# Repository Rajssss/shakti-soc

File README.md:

Central repository for Shakti SoC's
===================================

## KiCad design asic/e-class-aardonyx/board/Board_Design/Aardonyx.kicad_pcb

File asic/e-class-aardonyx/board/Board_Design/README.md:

This design is draft verison it not complete verision. 

This folder contains all board design related files.

## Directory Structure

├── Aardonyx.pro        # Kicad project                     
├── board               # Kicad pcb files for Aardonyx      
├── gerber              # Gerber files for Aardonyx         
├── library             # library(symbols) used for Aardonyx  
├── modules             # moudles(footprint lib, 3d model) used for Aardonyx    
├── schematic           # schematics for Aardonyx

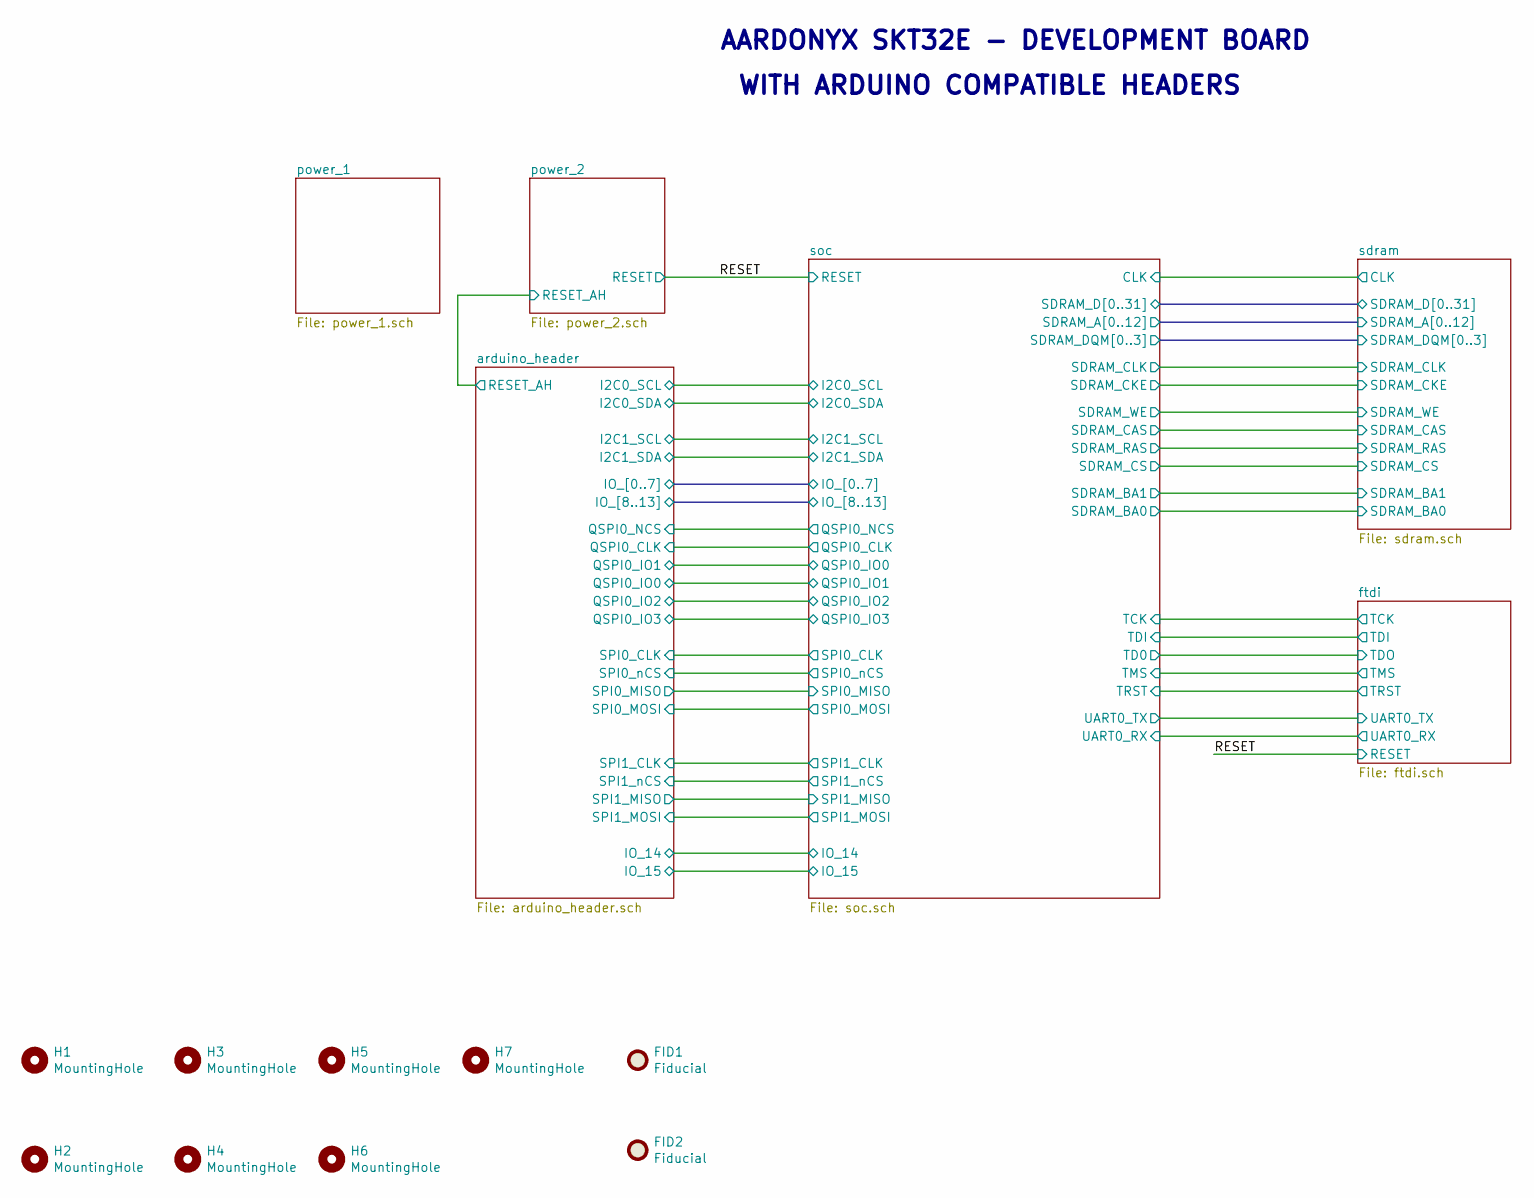
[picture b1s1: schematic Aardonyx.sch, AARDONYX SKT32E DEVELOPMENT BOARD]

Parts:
FID1, FID2: Fiducial; Fiducial_1.5mm_Mask3mm
H1, H2, H3, H4, H5, H6, H7: MountingHole; MountingHole_3.2mm_M3

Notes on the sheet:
AARDONYX SKT32E - DEVELOPMENT BOARD
WITH ARDUINO COMPATIBLE HEADERS

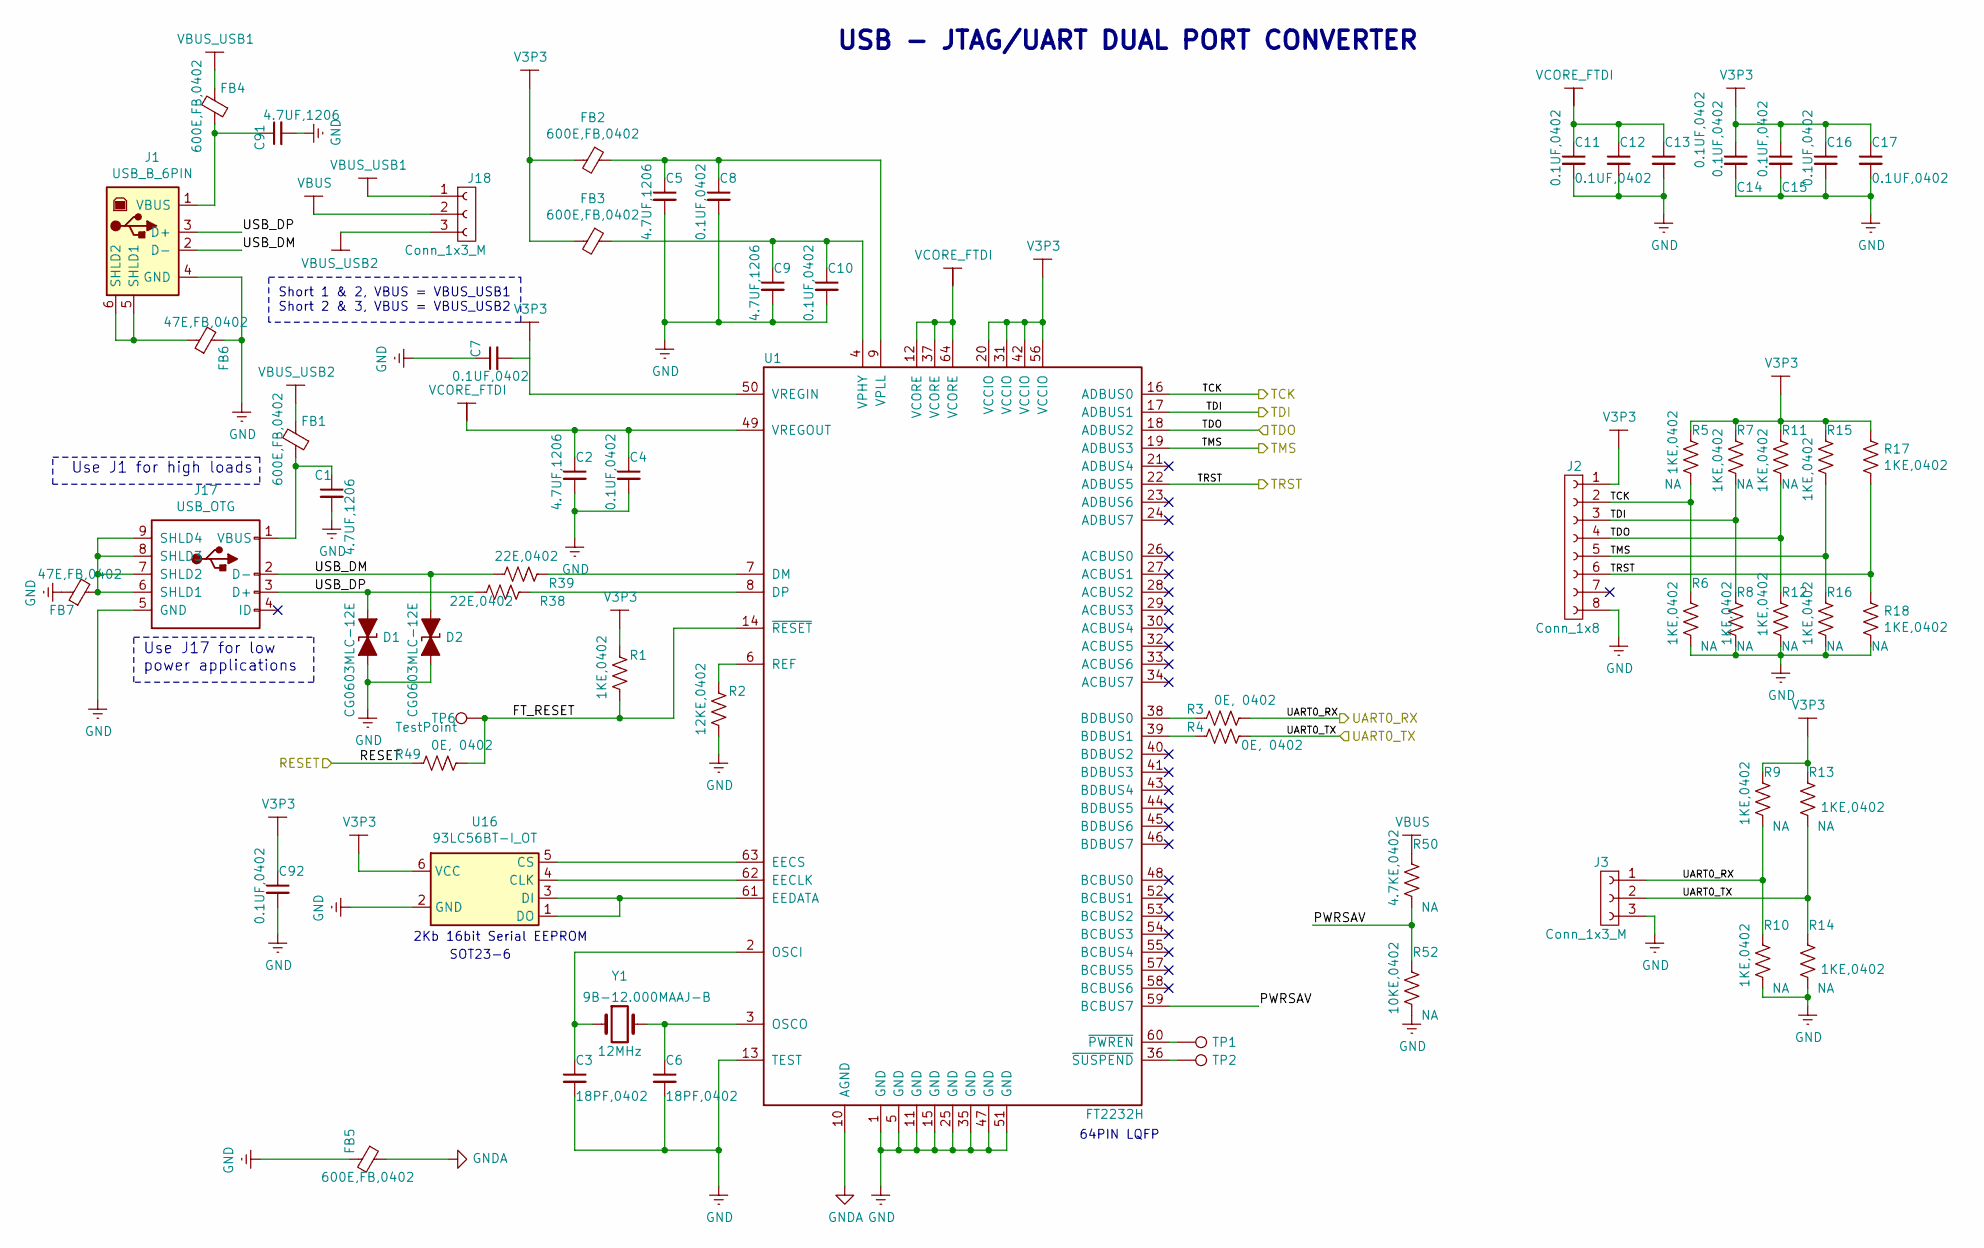
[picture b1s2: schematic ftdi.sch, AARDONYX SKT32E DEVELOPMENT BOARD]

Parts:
C1, C2, C5, C9, C91: 4.7UF,1206; C_1206_3216Metric; Manufactured Part Number T491A475K016AT; Digikey PartNumber 399-18027-1-ND
C3, C6: 18PF,0402; C_0402_1005Metric; Manufactured Part Number CC0201JRNPO9BN180; Digikey PartNumber 311-1386-1-ND
C4, C7, C8, C10, C11, C12, C13, C14, C15, C16, C17, C92: 0.1UF,0402; C_0402_1005Metric; Manufactured Part Number 04023C104JAT2A; Digikey PartNumber 478-10050-1-ND
D1, D2: CG0603MLC-12E; D_0603_1608Metric; Manufactured Part Number CG0603MLC-12E; Digikey PartNumber CG0603MLC-12ECT-ND
FB1, FB2, FB3, FB4, FB5: 600E,FB,0402; L_0402_1005Metric; Manufactured Part Number 7427927291; Digikey PartNumber 732-2388-1-ND
FB6, FB7: 47E,FB,0402; L_0402_1005Metric; Manufactured Part Number 742792608; Digikey PartNumber 732-1596-1-ND
J1: USB_B_6PIN; USB_B_OST_USB-B1HSxx_Horizontal; Manufactured Part Number 61729-0010BLF; Digikey PartNumber 609-1039-ND
J2: Conn_1x8; PinHeader_1x08_P2.54mm_Vertical; Manufactured Part Number 68000-408HLF; Digikey PartNumber 609-3264-ND
J3, J18: Conn_1x3_M; PinHeader_1x03_P2.54mm_Vertical; Manufactured Part Number 68000-203HLF; Digikey PartNumber 609-3464-ND
J17: USB_OTG; USB_Micro-B_Amphenol_10103594-0001LF_Horizontal; Manufactured Part Number 10118194-0001LF; Digikey PartNumber 609-4618-1-ND
R1: 1KE,0402; R_0402_1005Metric; Manufactured Part Number ERJ-2GEJ102X; Digikey PartNumber P1.0KJCT-ND
R2: 12KE,0402; R_0402_1005Metric; Manufactured Part Number ERA-2AEB123X; Digikey PartNumber P12KDCCT-ND
R3, R4, R49: 0E, 0402; R_0402_1005Metric; Manufactured Part Number CRCW04020000Z0ED; Digikey PartNumber 541-0.0JCT-ND
R5, R6, R7, R8, R9, R10, R11, R12, R13, R14, R15, R16, R17, R18: 1KE,0402; R_0402_1005Metric; Manufactured Part Number ERA-2AEB123X; Digikey PartNumber P1.0KJCT-ND
R38, R39: 22E,0402; R_0402_1005Metric; Manufactured Part Number RC0402FR-0722RL; Digikey PartNumber 311-22.0LRCT-ND
R50: 4.7KE,0402; R_0402_1005Metric; Manufactured Part Number RC0402JR-074K7L; Digikey PartNumber 311-4.7KJRCT-ND
R52: 10KE,0402; R_0402_1005Metric; Manufactured Part Number SG73S1ETTP103J; Digikey PartNumber 2019-SG73S1ETTP103JCT-ND
TP1, TP2, TP6: TestPoint; TestPoint_Pad_D1.0mm
U1: FT2232H; LQFP-64_10x10mm_P0.5mm; Manufactured Part Number FT2232HL-REEL; Digikey PartNumber 768-1024-1-ND
U16: 93LC56BT-I_OT; SOT-23-6; Manufactured Part Number 93LC56BT-I/OT; Digikey PartNumber 93LC56BT-I/OTCT-ND
Y1: 12MHz; Crystal_SMD_ROHS_CSM_7XDN_HandSoldering; Manufactured Part Number ECS-120-20-5PXDN-TR; Digikey PartNumber XC1298CT-ND

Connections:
/RESET: R49.1; also elsewhere on the board
/ftdi/FT_RESET: R1.2, R49.2, TP6.1, U1.14 (~RESET)
/ftdi/PWRSAV: R50.2, R52.1, U1.59 (BCBUS7)
/ftdi/TCK: J2.2, R5.2, R6.1, U1.16 (ADBUS0); also elsewhere on the board
/ftdi/TDI: J2.3, R7.2, R8.1, U1.17 (ADBUS1); also elsewhere on the board
/ftdi/TMS: J2.5, R15.2, R16.1, U1.19 (ADBUS3); also elsewhere on the board
/ftdi/TRST: J2.6, R17.2, R18.1, U1.22 (ADBUS5); also elsewhere on the board
/ftdi/UART0_RX: J3.1, R3.2, R9.2, R10.1; also elsewhere on the board
/ftdi/UART0_TX: J3.2, R4.2, R13.2, R14.1; also elsewhere on the board
/ftdi/USB_DM: D2.1 (A1), J1.2 (D-), J17.2 (D-), R39.2
/ftdi/USB_DP: D1.1 (A1), J1.3 (D+), J17.3 (D+), R38.2
/soc/TD0: J2.4, R11.2, R12.1, U1.18 (ADBUS2); also elsewhere on the board
GND: C1.2, C2.2, C3.2, C4.2, C5.2, C6.2, C7.1, C8.2, C9.2, C10.2, C11.2, C12.2, C13.2, C14.2, C15.2, C16.2, C17.2, C91.2, C92.2, D1.2 (A2), D2.2 (A2), FB5.2, FB6.2, FB7.1, J1.4 (GND), J2.8, J3.3, J17.5 (GND), R2.2, R6.2, R8.2, R10.2, R12.2, R14.2, R16.2, R18.2, R52.2, U1.1 (GND), U1.5 (GND), U1.11 (GND), U1.13 (TEST), U1.15 (GND), U1.25 (GND), U1.35 (GND), U1.47 (GND), U1.51 (GND), U16.2 (GND); also elsewhere on the board
GNDA: FB5.1, U1.10 (AGND)
unnamed: C1.1, FB1.1, J17.1 (VBUS)
unnamed: C3.1, U1.2 (OSCI), Y1.1
unnamed: C5.1, C8.1, FB2.1, U1.9 (VPLL)
unnamed: C6.1, U1.3 (OSCO), Y1.2
unnamed: C9.1, C10.1, FB3.1, U1.4 (VPHY)
unnamed: C91.1, FB4.1, J1.1 (VBUS)
unnamed: FB6.1, J1.5 (SHLD1), J1.6 (SHLD2)
unnamed: FB7.2, J17.6 (SHLD1), J17.7 (SHLD2), J17.8 (SHLD3), J17.9 (SHLD4)
unnamed: R2.1, U1.6 (REF)
unnamed: R3.1, U1.38 (BDBUS0)
unnamed: R4.1, U1.39 (BDBUS1)
unnamed: R38.1, U1.8 (DP)
unnamed: R39.1, U1.7 (DM)
unnamed: TP1.1, U1.60 (~PWREN)
unnamed: TP2.1, U1.36 (~SUSPEND)
unnamed: U1.61 (EEDATA), U16.1 (DO), U16.3 (DI)
unnamed: U1.62 (EECLK), U16.4 (CLK)
unnamed: U1.63 (EECS), U16.5 (CS)
V3P3: C7.2, C14.1, C15.1, C16.1, C17.1, C92.1, FB2.2, FB3.2, J2.1, R1.1, R5.1, R7.1, R9.1, R11.1, R13.1, R15.1, R17.1, U1.20 (VCCIO), U1.31 (VCCIO), U1.42 (VCCIO), U1.50 (VREGIN), U1.56 (VCCIO), U16.6 (VCC); also elsewhere on the board
VBUS: J18.2, R50.1; also elsewhere on the board
VBUS_USB1: FB4.2, J18.1
VBUS_USB2: FB1.2, J18.3
VCORE_FTDI: C2.1, C4.1, C11.1, C12.1, C13.1, U1.12 (VCORE), U1.37 (VCORE), U1.49 (VREGOUT), U1.64 (VCORE)

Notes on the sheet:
USB - JTAG/UART DUAL PORT CONVERTER
64PIN LQFP
2Kb 16bit Serial EEPROM
SOT23-6
Short 1 & 2, VBUS = VBUS_USB1 Short 2 & 3, VBUS = VBUS_USB2
Use J1 for high loads
Use J17 for low power applications

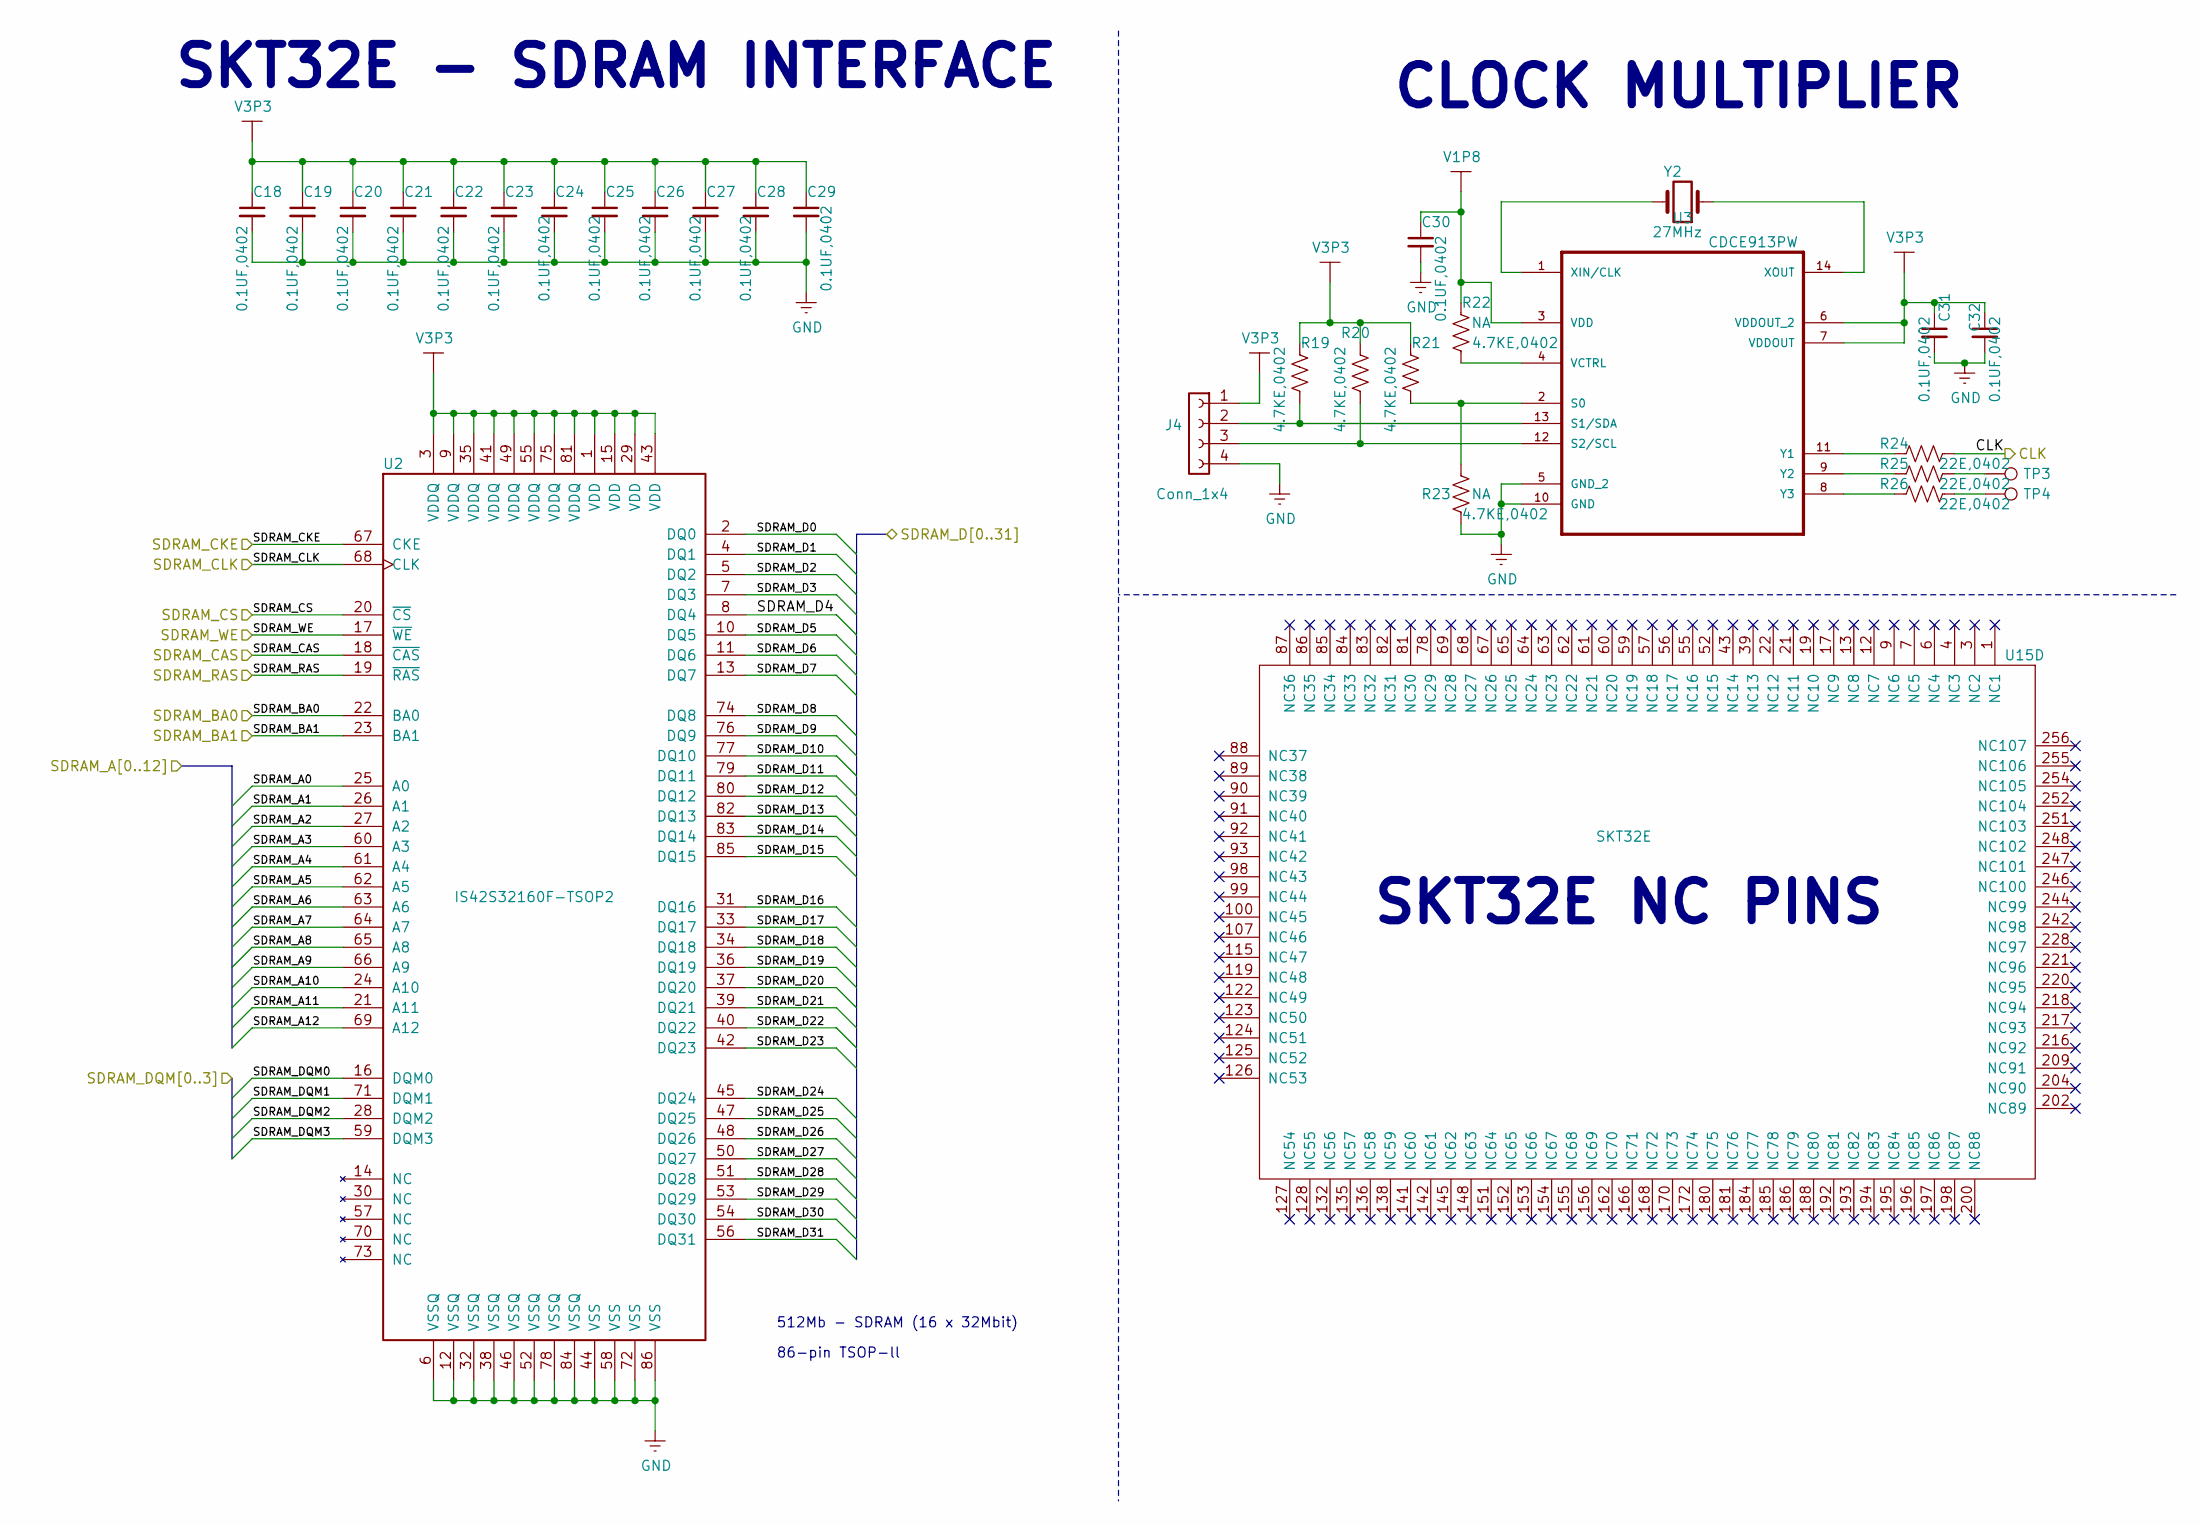
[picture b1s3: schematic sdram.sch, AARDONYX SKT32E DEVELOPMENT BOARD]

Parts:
C18, C19, C20, C21, C22, C23, C24, C25, C26, C27, C28, C29, C30, C31, C32: 0.1UF,0402; C_0402_1005Metric; Manufactured Part Number 04023C104JAT2A; Digikey PartNumber 478-10050-1-ND
J4: Conn_1x4; PinHeader_1x04_P2.54mm_Vertical; Manufactured Part Number 68000-404HLF; Digikey PartNumber 609-3262-ND
R19, R20, R21, R22, R23: 4.7KE,0402; R_0402_1005Metric; Manufactured Part Number RC0402JR-074K7L; Digikey PartNumber 311-4.7KJRCT-ND
R24, R25, R26: 22E,0402; R_0402_1005Metric; Manufactured Part Number RC0402FR-0722RL; Digikey PartNumber 311-22.0LRCT-ND
TP3, TP4: TestPoint; TestPoint_Pad_D1.0mm
U2: IS42S32160F-TSOP2; TSSOP-II-86_10.16x22.2mm_P0.5mm; Manufactured Part Number IS42S32160F-7TLI; Digikey PartNumber 706-1417-5-ND
U3: CDCE913PW; TSSOP-14_4.4x5mm_P0.65mm; Manufactured Part Number CDCE913PWR; Digikey PartNumber 296-38908-1-ND
U15: SKT32E; SKT32E_IITM; Manufactured Part Number SKT32E; Digikey PartNumber NA
Y2: 27MHz; Crystal_SMD_ROHS_CSM_7XDN_HandSoldering; Manufactured Part Number ECS-270-18-5PX-F-TR; Digikey PartNumber XC1002CT-ND

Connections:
/sdram/CLK: R24.1; also elsewhere on the board
/sdram/SDRAM_A0: U2.25 (A0); also elsewhere on the board
/sdram/SDRAM_A1: U2.26 (A1); also elsewhere on the board
/sdram/SDRAM_A2: U2.27 (A2); also elsewhere on the board
/sdram/SDRAM_A3: U2.60 (A3); also elsewhere on the board
/sdram/SDRAM_A4: U2.61 (A4); also elsewhere on the board
/sdram/SDRAM_A5: U2.62 (A5); also elsewhere on the board
/sdram/SDRAM_A6: U2.63 (A6); also elsewhere on the board
/sdram/SDRAM_A7: U2.64 (A7); also elsewhere on the board
/sdram/SDRAM_A8: U2.65 (A8); also elsewhere on the board
/sdram/SDRAM_A9: U2.66 (A9); also elsewhere on the board
/sdram/SDRAM_A10: U2.24 (A10); also elsewhere on the board
/sdram/SDRAM_A11: U2.21 (A11); also elsewhere on the board
/sdram/SDRAM_A12: U2.69 (A12); also elsewhere on the board
/sdram/SDRAM_BA0: U2.22 (BA0); also elsewhere on the board
/sdram/SDRAM_BA1: U2.23 (BA1); also elsewhere on the board
/sdram/SDRAM_CAS: U2.18 (~CAS); also elsewhere on the board
/sdram/SDRAM_CKE: U2.67 (CKE); also elsewhere on the board
/sdram/SDRAM_CLK: U2.68 (CLK); also elsewhere on the board
/sdram/SDRAM_CS: U2.20 (~CS); also elsewhere on the board
/sdram/SDRAM_D0: U2.2 (DQ0); also elsewhere on the board
/sdram/SDRAM_D1: U2.4 (DQ1); also elsewhere on the board
/sdram/SDRAM_D2: U2.5 (DQ2); also elsewhere on the board
/sdram/SDRAM_D3: U2.7 (DQ3); also elsewhere on the board
/sdram/SDRAM_D4: U2.8 (DQ4); also elsewhere on the board
/sdram/SDRAM_D5: U2.10 (DQ5); also elsewhere on the board
/sdram/SDRAM_D6: U2.11 (DQ6); also elsewhere on the board
/sdram/SDRAM_D7: U2.13 (DQ7); also elsewhere on the board
/sdram/SDRAM_D8: U2.74 (DQ8); also elsewhere on the board
/sdram/SDRAM_D9: U2.76 (DQ9); also elsewhere on the board
/sdram/SDRAM_D10: U2.77 (DQ10); also elsewhere on the board
/sdram/SDRAM_D11: U2.79 (DQ11); also elsewhere on the board
/sdram/SDRAM_D12: U2.80 (DQ12); also elsewhere on the board
/sdram/SDRAM_D13: U2.82 (DQ13); also elsewhere on the board
/sdram/SDRAM_D14: U2.83 (DQ14); also elsewhere on the board
/sdram/SDRAM_D15: U2.85 (DQ15); also elsewhere on the board
/sdram/SDRAM_D16: U2.31 (DQ16); also elsewhere on the board
/sdram/SDRAM_D17: U2.33 (DQ17); also elsewhere on the board
/sdram/SDRAM_D18: U2.34 (DQ18); also elsewhere on the board
/sdram/SDRAM_D19: U2.36 (DQ19); also elsewhere on the board
/sdram/SDRAM_D20: U2.37 (DQ20); also elsewhere on the board
/sdram/SDRAM_D21: U2.39 (DQ21); also elsewhere on the board
/sdram/SDRAM_D22: U2.40 (DQ22); also elsewhere on the board
/sdram/SDRAM_D23: U2.42 (DQ23); also elsewhere on the board
/sdram/SDRAM_D24: U2.45 (DQ24); also elsewhere on the board
/sdram/SDRAM_D25: U2.47 (DQ25); also elsewhere on the board
/sdram/SDRAM_D26: U2.48 (DQ26); also elsewhere on the board
/sdram/SDRAM_D27: U2.50 (DQ27); also elsewhere on the board
/sdram/SDRAM_D28: U2.51 (DQ28); also elsewhere on the board
/sdram/SDRAM_D29: U2.53 (DQ29); also elsewhere on the board
/sdram/SDRAM_D30: U2.54 (DQ30); also elsewhere on the board
/sdram/SDRAM_D31: U2.56 (DQ31); also elsewhere on the board
/sdram/SDRAM_DQM0: U2.16 (DQM0); also elsewhere on the board
/sdram/SDRAM_DQM1: U2.71 (DQM1); also elsewhere on the board
/sdram/SDRAM_DQM2: U2.28 (DQM2); also elsewhere on the board
/sdram/SDRAM_DQM3: U2.59 (DQM3); also elsewhere on the board
/sdram/SDRAM_RAS: U2.19 (~RAS); also elsewhere on the board
/sdram/SDRAM_WE: U2.17 (~WE); also elsewhere on the board
GND: C18.2, C19.2, C20.2, C21.2, C22.2, C23.2, C24.2, C25.2, C26.2, C27.2, C28.2, C29.2, C30.2, C31.2, C32.2, J4.4, R23.2, U2.6 (VSSQ), U2.12 (VSSQ), U2.32 (VSSQ), U2.38 (VSSQ), U2.44 (VSS), U2.46 (VSSQ), U2.52 (VSSQ), U2.58 (VSS), U2.72 (VSS), U2.78 (VSSQ), U2.84 (VSSQ), U2.86 (VSS), U3.5 (GND_2), U3.10 (GND); also elsewhere on the board
unnamed: J4.2, R19.2, U3.13 (S1/SDA)
unnamed: J4.3, R20.2, U3.12 (S2/SCL)
unnamed: R21.2, R23.1, U3.2 (S0)
unnamed: R22.2, U3.4 (VCTRL)
unnamed: R24.2, U3.11 (Y1)
unnamed: R25.1, TP3.1
unnamed: R25.2, U3.9 (Y2)
unnamed: R26.1, TP4.1
unnamed: R26.2, U3.8 (Y3)
unnamed: U3.1 (XIN/CLK), Y2.2
unnamed: U3.14 (XOUT), Y2.1
V1P8: C30.1, R22.1, U3.3 (VDD); also elsewhere on the board
V3P3: C18.1, C19.1, C20.1, C21.1, C22.1, C23.1, C24.1, C25.1, C26.1, C27.1, C28.1, C29.1, C31.1, C32.1, J4.1, R19.1, R20.1, R21.1, U2.1 (VDD), U2.3 (VDDQ), U2.9 (VDDQ), U2.15 (VDD), U2.29 (VDD), U2.35 (VDDQ), U2.41 (VDDQ), U2.43 (VDD), U2.49 (VDDQ), U2.55 (VDDQ), U2.75 (VDDQ), U2.81 (VDDQ), U3.6 (VDDOUT_2), U3.7 (VDDOUT); also elsewhere on the board

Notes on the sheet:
CLOCK MULTIPLIER
SKT32E - SDRAM INTERFACE
SKT32E NC PINS
512Mb - SDRAM (16 x 32Mbit)
86-pin TSOP-ll

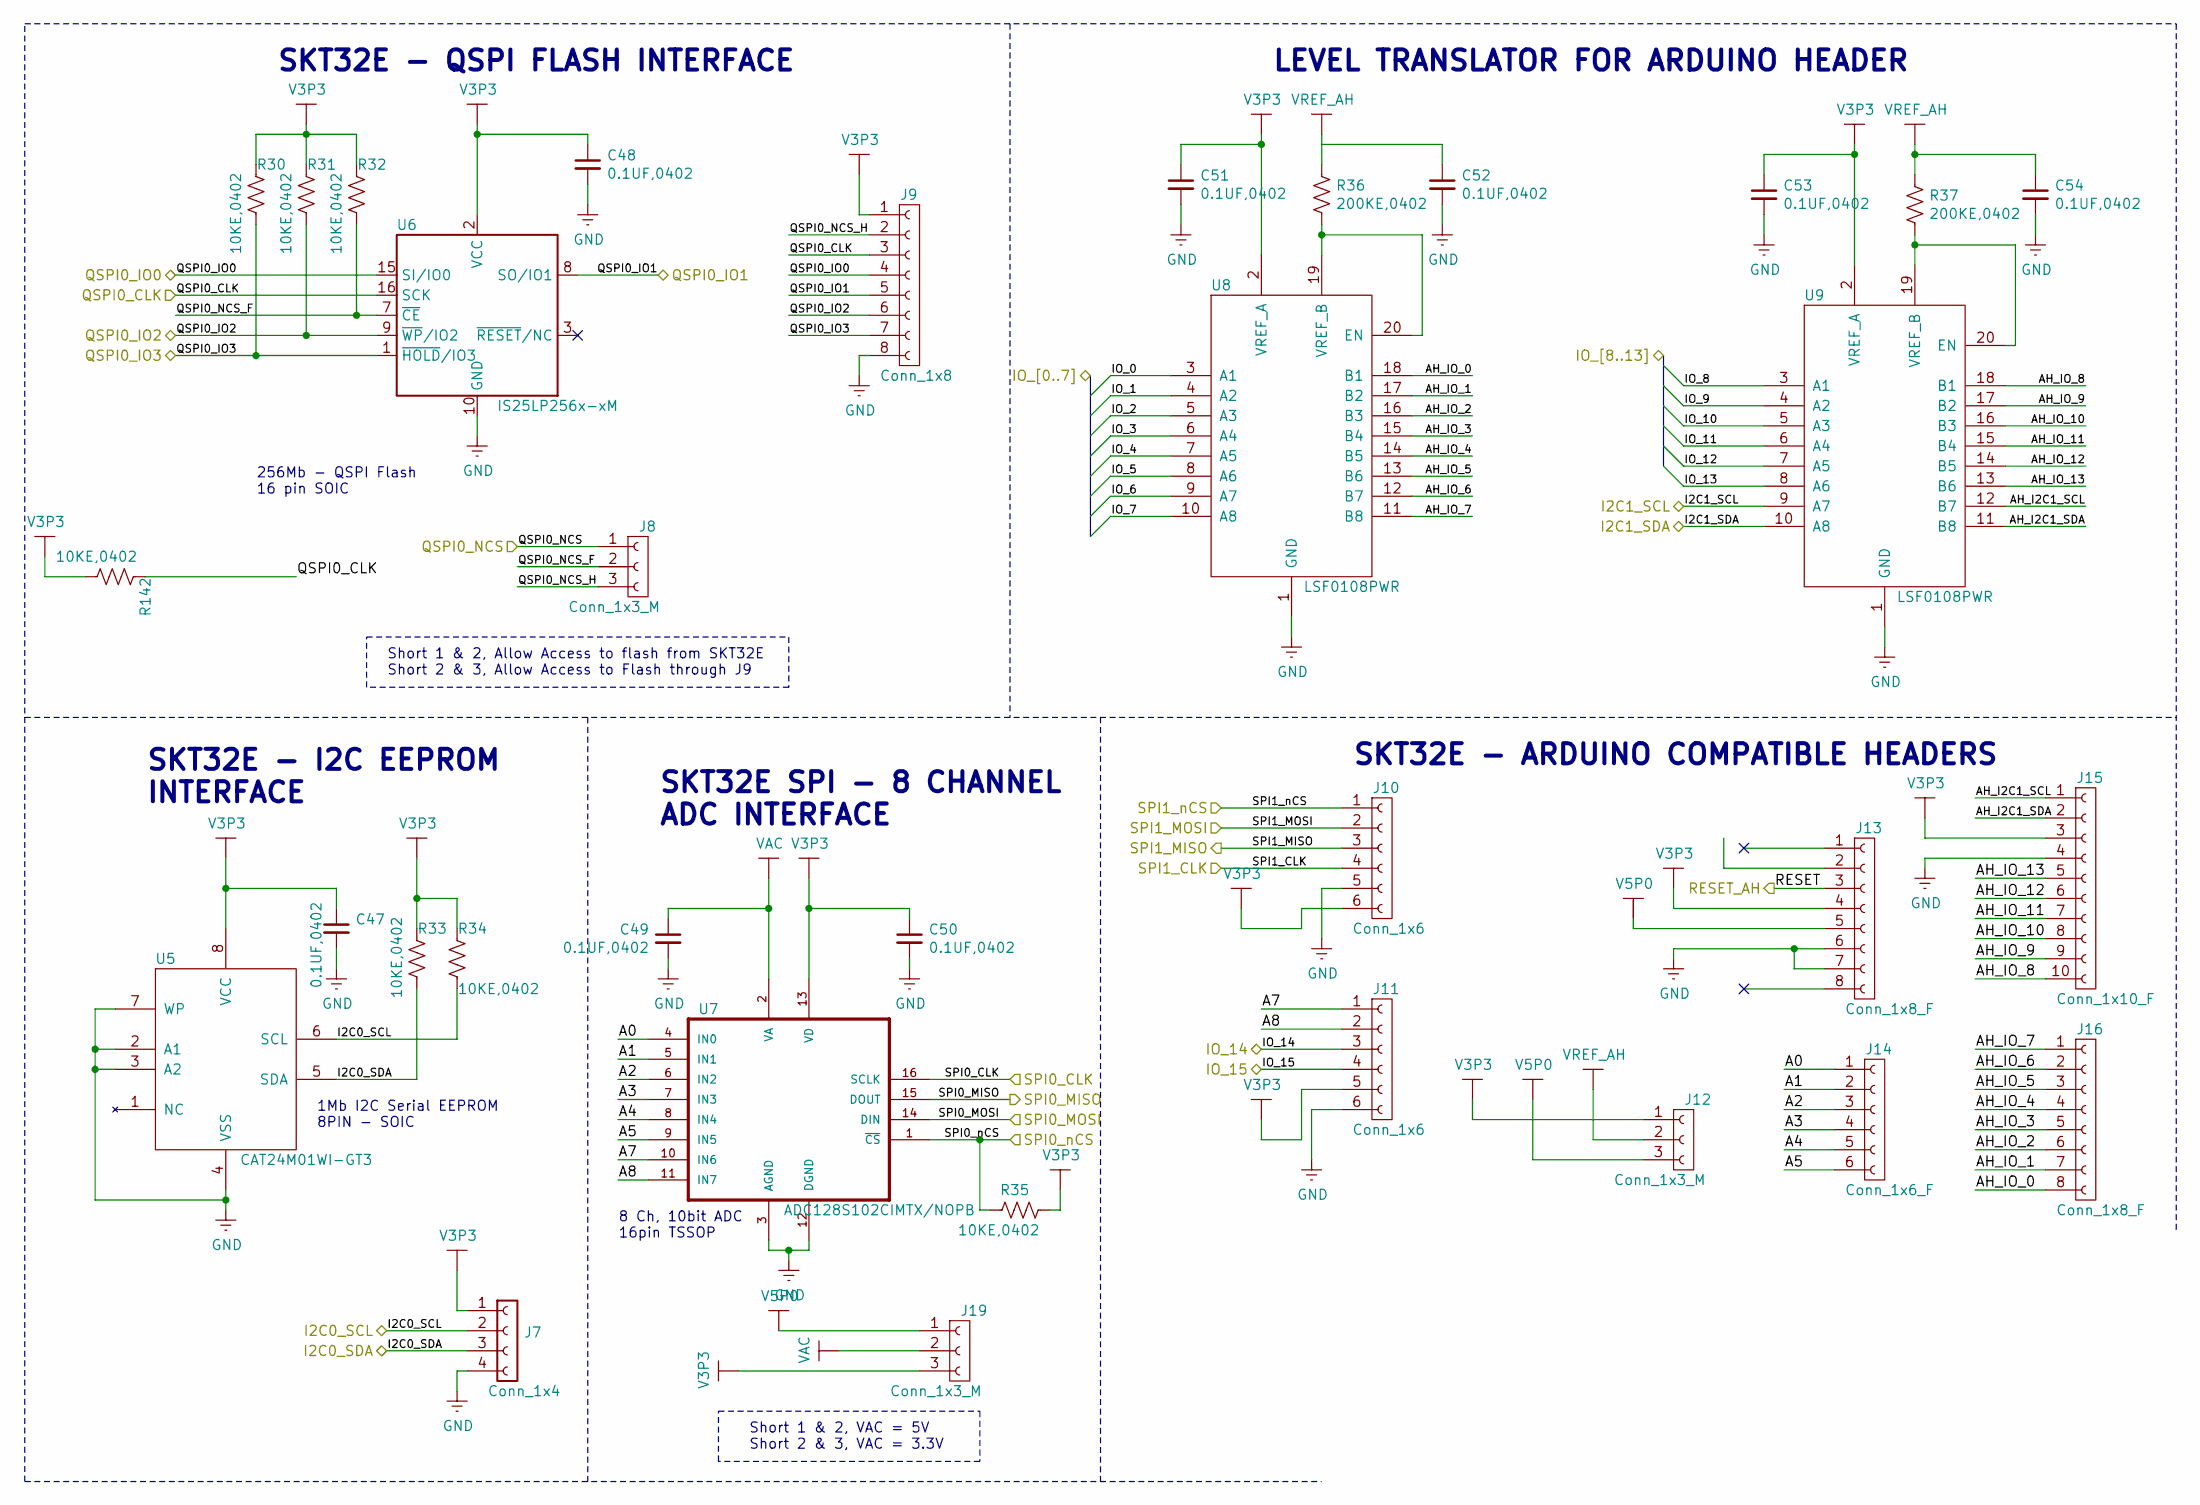
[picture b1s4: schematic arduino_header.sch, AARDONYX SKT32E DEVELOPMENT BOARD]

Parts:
C47, C48, C49, C50, C51, C52, C53, C54: 0.1UF,0402; C_0402_1005Metric; Manufactured Part Number 04023C104JAT2A; Digikey PartNumber 478-10050-1-ND
J7: Conn_1x4; PinHeader_1x04_P2.54mm_Vertical; Manufactured Part Number 68000-404HLF; Digikey PartNumber 609-3262-ND
J8, J12, J19: Conn_1x3_M; PinHeader_1x03_P2.54mm_Vertical; Manufactured Part Number 68000-203HLF; Digikey PartNumber 609-3464-ND
J9: Conn_1x8; PinHeader_1x08_P2.54mm_Vertical; Manufactured Part Number 68000-408HLF; Digikey PartNumber 609-3264-ND
J10, J11: Conn_1x6; PinHeader_1x06_P2.54mm_Vertical; Manufactured Part Number 68000-406HLF; Digikey PartNumber 609-3263-ND
J13, J16: Conn_1x8_F; PinSocket_1x08_P2.54mm_Vertical; Manufactured Part Number 68685-308LF; Digikey PartNumber 609-3589-ND
J14: Conn_1x6_F; PinSocket_1x06_P2.54mm_Vertical; Manufactured Part Number 75915-306LF; Digikey PartNumber 609-3558-ND
J15: Conn_1x10_F; PinSocket_1x10_P2.54mm_Vertical; Manufactured Part Number 68685-310LF; Digikey PartNumber 609-3584-ND
R30, R31, R32, R33, R34, R35, R142: 10KE,0402; R_0402_1005Metric; Manufactured Part Number SG73S1ETTP103J; Digikey PartNumber 2019-SG73S1ETTP103JCT-ND
R36, R37: 200KE,0402; R_0402_1005Metric; Manufactured Part Number RN73H1ETTP2003B25; Digikey PartNumber 2019-RN73H1ETTP2003B25CT-ND
U5: CAT24M01WI-GT3; SOIC-8_3.9x4.9mm_P1.27mm; Manufactured Part Number CAT24M01XI-T2; Digikey PartNumber CAT24M01XI-T2OSCT-ND
U6: IS25LP256x-xM; SOIC-16W_7.5x10.3mm_P1.27mm; Manufactured Part Number IS25LP256D-JMLE; Digikey PartNumber 706-1611-ND
U7: ADC128S102CIMTX/NOPB; TSSOP-16_4.4x5mm_P0.65mm; Manufactured Part Number ADC128S102CIMTX/NOPB; Digikey PartNumber 296-41184-1-ND
U8, U9: LSF0108PWR; TSSOP-20_4.4x6.5mm_P0.65mm; Manufactured Part Number LSF0108PWR; Digikey PartNumber 296-37828-1-ND

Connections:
/arduino_header/A0: J14.1, U7.4 (IN0)
/arduino_header/A1: J14.2, U7.5 (IN1)
/arduino_header/A2: J14.3, U7.6 (IN2)
/arduino_header/A3: J14.4, U7.7 (IN3)
/arduino_header/A4: J14.5, U7.8 (IN4)
/arduino_header/A5: J14.6, U7.9 (IN5)
/arduino_header/A7: J11.1, U7.10 (IN6)
/arduino_header/A8: J11.2, U7.11 (IN7)
/arduino_header/AH_I2C1_SCL: J15.1, U9.12 (B7)
/arduino_header/AH_I2C1_SDA: J15.2, U9.11 (B8)
/arduino_header/AH_IO_0: J16.8, U8.18 (B1)
/arduino_header/AH_IO_1: J16.7, U8.17 (B2)
/arduino_header/AH_IO_2: J16.6, U8.16 (B3)
/arduino_header/AH_IO_3: J16.5, U8.15 (B4)
/arduino_header/AH_IO_4: J16.4, U8.14 (B5)
/arduino_header/AH_IO_5: J16.3, U8.13 (B6)
/arduino_header/AH_IO_6: J16.2, U8.12 (B7)
/arduino_header/AH_IO_7: J16.1, U8.11 (B8)
/arduino_header/AH_IO_8: J15.10, U9.18 (B1)
/arduino_header/AH_IO_9: J15.9, U9.17 (B2)
/arduino_header/AH_IO_10: J15.8, U9.16 (B3)
/arduino_header/AH_IO_11: J15.7, U9.15 (B4)
/arduino_header/AH_IO_12: J15.6, U9.14 (B5)
/arduino_header/AH_IO_13: J15.5, U9.13 (B6)
/arduino_header/I2C0_SCL: J7.2, R34.2, U5.6 (SCL); also elsewhere on the board
/arduino_header/I2C0_SDA: J7.3, R33.2, U5.5 (SDA); also elsewhere on the board
/arduino_header/I2C1_SCL: U9.9 (A7); also elsewhere on the board
/arduino_header/I2C1_SDA: U9.10 (A8); also elsewhere on the board
/arduino_header/IO_0: U8.3 (A1); also elsewhere on the board
/arduino_header/IO_1: U8.4 (A2); also elsewhere on the board
/arduino_header/IO_2: U8.5 (A3); also elsewhere on the board
/arduino_header/IO_3: U8.6 (A4); also elsewhere on the board
/arduino_header/IO_4: U8.7 (A5); also elsewhere on the board
/arduino_header/IO_5: U8.8 (A6); also elsewhere on the board
/arduino_header/IO_6: U8.9 (A7); also elsewhere on the board
/arduino_header/IO_7: U8.10 (A8); also elsewhere on the board
/arduino_header/IO_8: U9.3 (A1); also elsewhere on the board
/arduino_header/IO_9: U9.4 (A2); also elsewhere on the board
/arduino_header/IO_10: U9.5 (A3); also elsewhere on the board
/arduino_header/IO_11: U9.6 (A4); also elsewhere on the board
/arduino_header/IO_12: U9.7 (A5); also elsewhere on the board
/arduino_header/IO_13: U9.8 (A6); also elsewhere on the board
/arduino_header/IO_14: J11.3; also elsewhere on the board
/arduino_header/IO_15: J11.4; also elsewhere on the board
/arduino_header/QSPI0_CLK: J9.3, R142.1, U6.16 (SCK); also elsewhere on the board
/arduino_header/QSPI0_IO0: J9.4, U6.15 (SI/IO0); also elsewhere on the board
/arduino_header/QSPI0_IO2: J9.6, R31.2, U6.9 (~WP~/IO2); also elsewhere on the board
/arduino_header/QSPI0_IO3: J9.7, R30.2, U6.1 (~HOLD~/IO3); also elsewhere on the board
/arduino_header/QSPI0_NCS: J8.1; also elsewhere on the board
/arduino_header/QSPI0_NCS_F: J8.2, R32.2, U6.7 (~CE)
/arduino_header/QSPI0_NCS_H: J8.3, J9.2
/arduino_header/RESET_AH: J13.3; also elsewhere on the board
/arduino_header/SPI0_CLK: U7.16 (SCLK); also elsewhere on the board
/arduino_header/SPI0_MISO: U7.15 (DOUT); also elsewhere on the board
/arduino_header/SPI0_MOSI: U7.14 (DIN); also elsewhere on the board
/arduino_header/SPI0_nCS: R35.1, U7.1 (~CS); also elsewhere on the board
/arduino_header/SPI1_CLK: J10.4; also elsewhere on the board
/arduino_header/SPI1_MISO: J10.3; also elsewhere on the board
/arduino_header/SPI1_MOSI: J10.2; also elsewhere on the board
/arduino_header/SPI1_nCS: J10.1; also elsewhere on the board
/soc/QSPI0_IO0: J9.5, U6.8 (SO/IO1); also elsewhere on the board
GND: C47.2, C48.2, C49.2, C50.2, C51.2, C52.2, C53.2, C54.2, J7.4, J9.8, J10.5, J11.6, J13.6, J13.7, J15.4, U5.2 (A1), U5.3 (A2), U5.4 (VSS), U5.7 (WP), U6.10 (GND), U7.3 (AGND), U7.12 (DGND), U8.1 (GND), U9.1 (GND); also elsewhere on the board
unnamed: R36.2, U8.19 (VREF_B), U8.20 (EN)
unnamed: R37.2, U9.19 (VREF_B), U9.20 (EN)
V3P3: C47.1, C48.1, C50.1, C51.1, C53.1, J7.1, J9.1, J10.6, J11.5, J12.1, J13.4, J15.3, J19.3, R30.1, R31.1, R32.1, R33.1, R34.1, R35.2, R142.2, U5.8 (VCC), U6.2 (VCC), U7.13 (VD), U8.2 (VREF_A), U9.2 (VREF_A); also elsewhere on the board
V5P0: J12.3, J13.5, J19.1; also elsewhere on the board
VAC: C49.1, J19.2, U7.2 (VA)
VREF_AH: C52.1, C54.1, J12.2, R36.1, R37.1

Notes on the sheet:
SKT32E - QSPI FLASH INTERFACE
SKT32E - I2C EEPROM INTERFACE
LEVEL TRANSLATOR FOR ARDUINO HEADER
SKT32E - ARDUINO COMPATIBLE HEADERS
SKT32E SPI - 8 CHANNEL ADC INTERFACE
256Mb - QSPI Flash 16 pin SOIC
1Mb I2C Serial EEPROM 8PIN - SOIC
8 Ch, 10bit ADC 16pin TSSOP
Short 1 & 2, VAC = 5V Short 2 & 3, VAC = 3.3V
Short 1 & 2, Allow Access to flash from SKT32E Short 2 & 3, Allow Access to Flash through J9
